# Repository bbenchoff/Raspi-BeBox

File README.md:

# Raspi-BeBox
## A Raspberry Pi case that looks like a wee BeBox

There are several components of the BeBox, including 3D printed (filament), 3D printed (SLA), circuit boards, and random stuff picked up from Amazon:

### BlinkenPanel
The BlinkenPanel displays CPU usage on 16 LEDs shinging through the front. The [project is shared on OSHPark](https://oshpark.com/shared_projects/XPZorljf). Other components needed for this are:

* Green Square LEDs - Part Number SSL-LX3353GD
* I2C GPIO expander - MCP23017-E/SP
* Resistors of various sort - 0805
* DC Fan 5V - any 30mm fan for a Raspberry Pi

### Front panel
The heart of the BeBox - a front panel with Blinkenlights. This [is available on Shapeways](https://www.shapeways.com/product/FETJ2WU6V/raspi-bebox-face?optionId=224175918) or in the 3D files folder of this repository. Print with gray resin.

### Case Badge
...Comes from [Case Badges](https://www.case-badges.com), have them make a 0.75" square domed badge of the images in the /Graphics folder of this repository

### Interior. 
The case is designed for a Raspberry Pi 4, along with a dual microHDMI adapter board:

* [Buy these adapter boards](https://www.amazon.com/gp/product/B08V5MXLS6)
* [and this USB-C right angle adapter](https://www.amazon.com/gp/product/B086W2LTGY)

Screw bosses are sized for No. 4 screws.

## Assembly

Insert the LEDs in one side of the front panel. The anode (+) goes toward the middle. Bend the cathode (-) out. Fit the PCB with only the anodes of one side installed. Glue is recommended to hold the LEDs in place.

Install the other side of the LEDs, anode only.

Mount the PCB to the front panel with screws. Solder the anodes of the LEDs. Bend the cathode legs around the PCB to the other LED solder pads.

That's it! That's the easiest way to assemble this thing. Now write some python for the blinkenlights.

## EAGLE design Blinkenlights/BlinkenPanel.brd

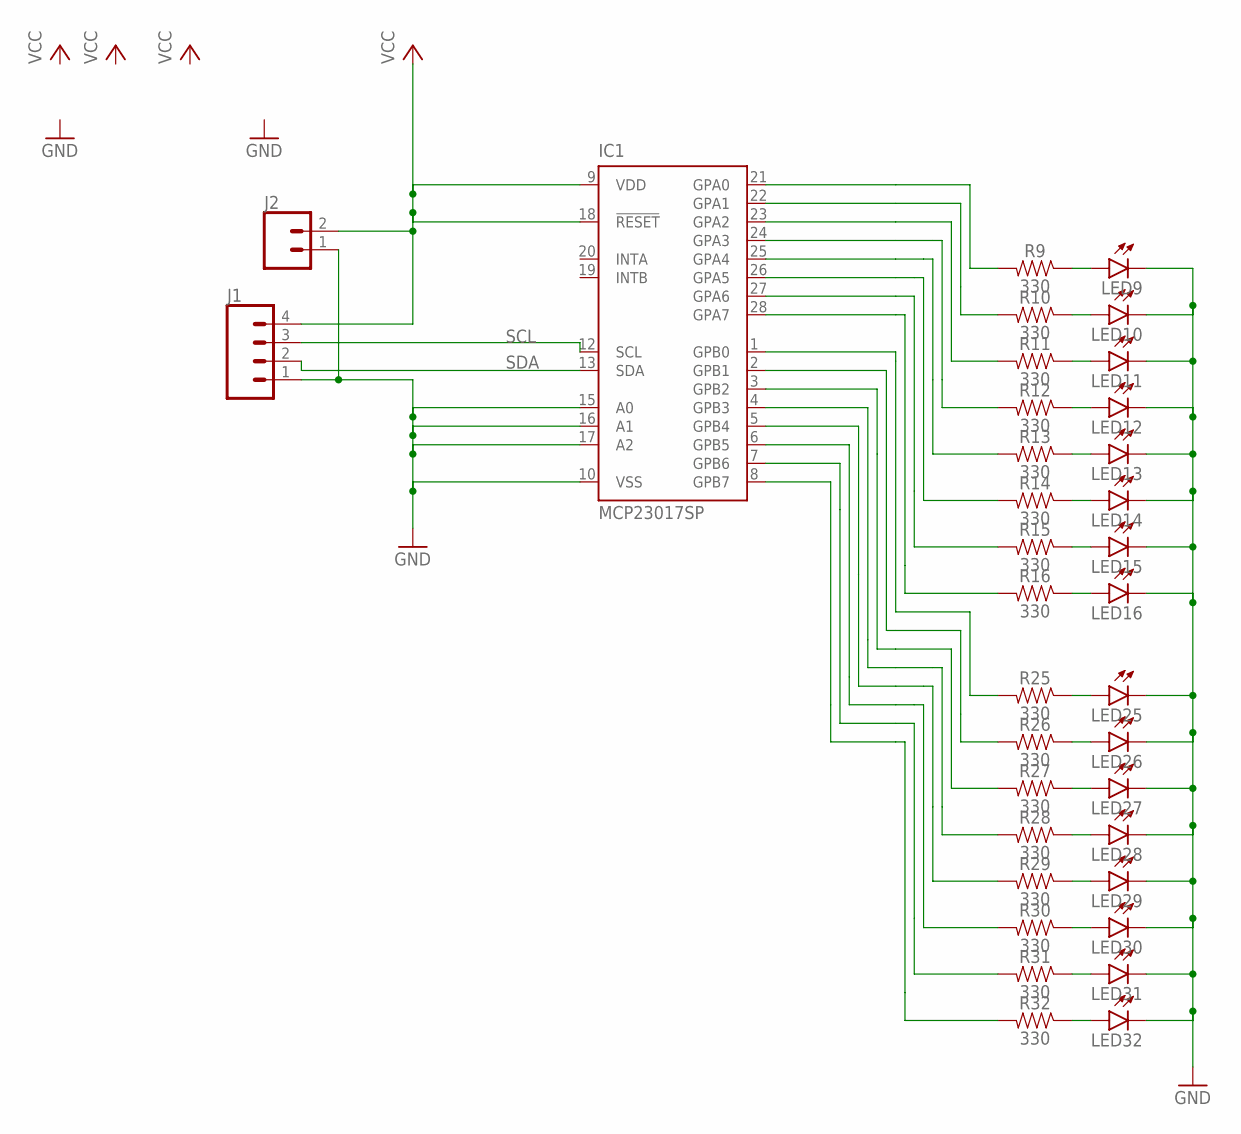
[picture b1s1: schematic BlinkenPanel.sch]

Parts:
IC1: MCP23017SP; DIL28-3
J1: CONN_04LOCK; 1X04_LOCK
J2: CONN_02; 1X02
LED9, LED10, LED11, LED12, LED13, LED14, LED15, LED16, LED25, LED26, LED27, LED28, LED29, LED30, LED31, LED32: LED3MM
R9, R10, R11, R12, R13, R14, R15, R16, R25, R26, R27, R28, R29, R30, R31, R32: 330; 0603

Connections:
GND: IC1.10 (VSS), IC1.15 (A0), IC1.16 (A1), IC1.17 (A2), J1.1, J2.1, LED9.K (C), LED10.K (C), LED11.K (C), LED12.K (C), LED13.K (C), LED14.K (C), LED15.K (C), LED16.K (C), LED25.K (C), LED26.K (C), LED27.K (C), LED28.K (C), LED29.K (C), LED30.K (C), LED31.K (C), LED32.K (C)
unnamed: LED9.A, R9.1
unnamed: LED10.A, R10.1
unnamed: LED11.A, R11.1
unnamed: LED12.A, R12.1
unnamed: LED13.A, R13.1
unnamed: LED14.A, R14.1
unnamed: LED15.A, R15.1
unnamed: LED16.A, R16.1
unnamed: IC1.21 (GPA0), R9.2
unnamed: IC1.22 (GPA1), R10.2
unnamed: IC1.23 (GPA2), R11.2
unnamed: IC1.24 (GPA3), R12.2
unnamed: IC1.25 (GPA4), R13.2
unnamed: IC1.26 (GPA5), R14.2
unnamed: IC1.27 (GPA6), R15.2
unnamed: IC1.28 (GPA7), R16.2
unnamed: LED25.A, R25.1
unnamed: LED26.A, R26.1
unnamed: LED27.A, R27.1
unnamed: LED28.A, R28.1
unnamed: LED29.A, R29.1
unnamed: LED30.A, R30.1
unnamed: LED31.A, R31.1
unnamed: LED32.A, R32.1
unnamed: IC1.1 (GPB0), R25.2
unnamed: IC1.2 (GPB1), R26.2
unnamed: IC1.3 (GPB2), R27.2
unnamed: IC1.4 (GPB3), R28.2
unnamed: IC1.5 (GPB4), R29.2
unnamed: IC1.6 (GPB5), R30.2
unnamed: IC1.7 (GPB6), R31.2
unnamed: IC1.8 (GPB7), R32.2
SCL: IC1.12 (SCL), J1.3
SDA: IC1.13 (SDA), J1.2
VCC: IC1.9 (VDD), IC1.18 (!RESET), J1.4, J2.2

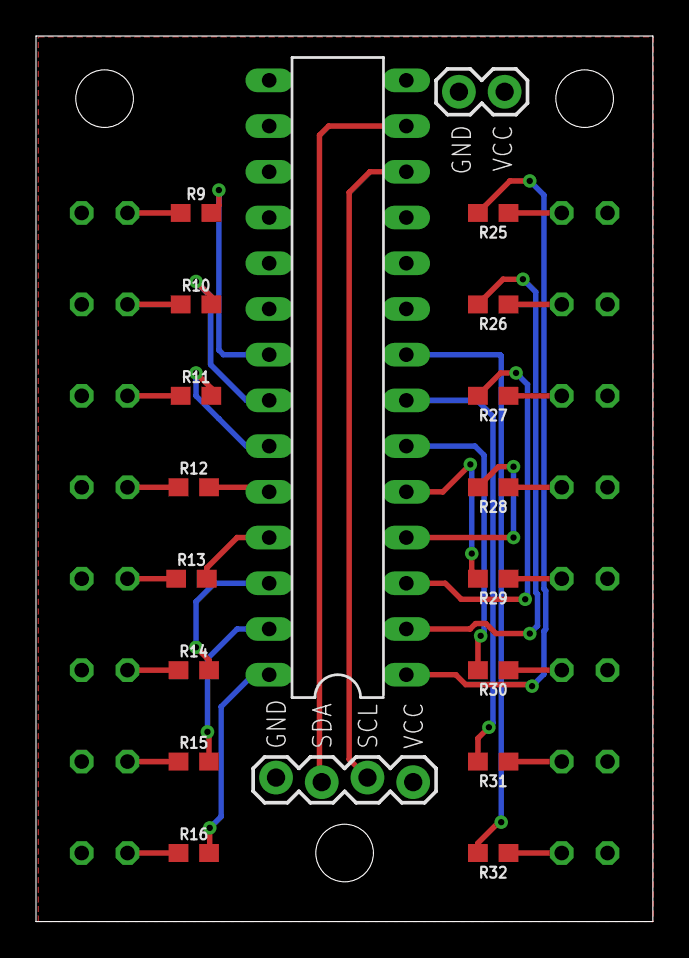
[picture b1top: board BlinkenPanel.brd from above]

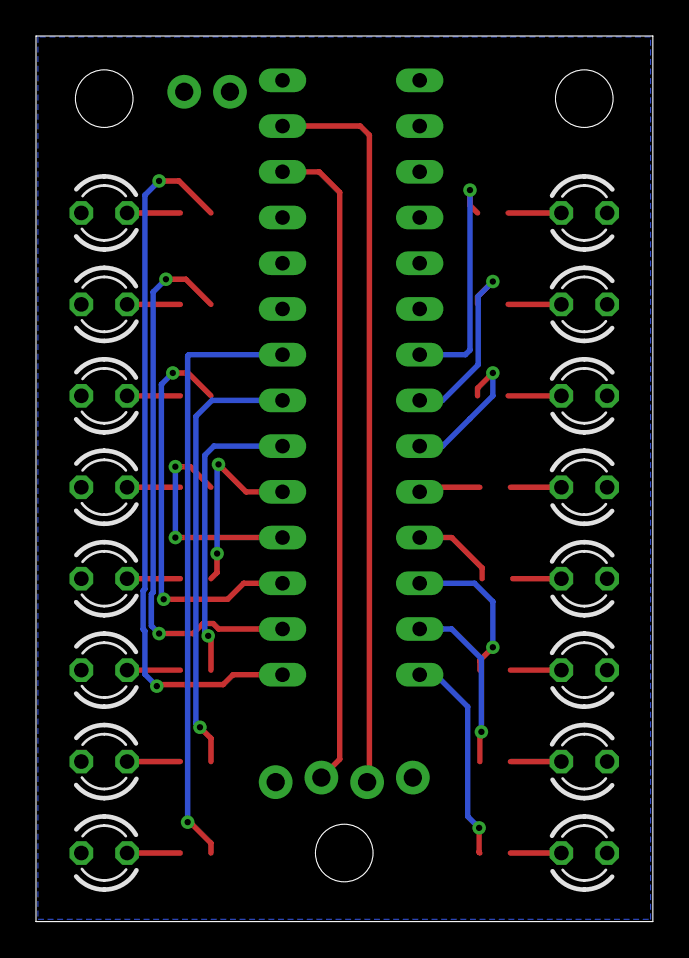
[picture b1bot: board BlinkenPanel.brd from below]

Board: 2 copper layers, 34.3 x 49.2 mm, 35 parts (16 on the bottom side), 36 nets.

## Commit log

2021-07-29 make a blinkenpanel
2021-08-03 added prints, fixed blinkenpanel
2021-08-12 updated 3D prints
2021-08-12 added without serial
2021-08-29 Added assembly instructions
2021-08-29 README.md: fix link to case-badges.com
2022-02-27 Add Haiku Logo to the repository
    I know, the ARM port isn't ready yet. But just in case
2022-12-13 update other computers

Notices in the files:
parts and their libraries:
SparkFun-Resistors: Licensing: Creative Commons ShareAlike 4.0 International - https://creativecommons.org/licenses/by-sa/4.0
